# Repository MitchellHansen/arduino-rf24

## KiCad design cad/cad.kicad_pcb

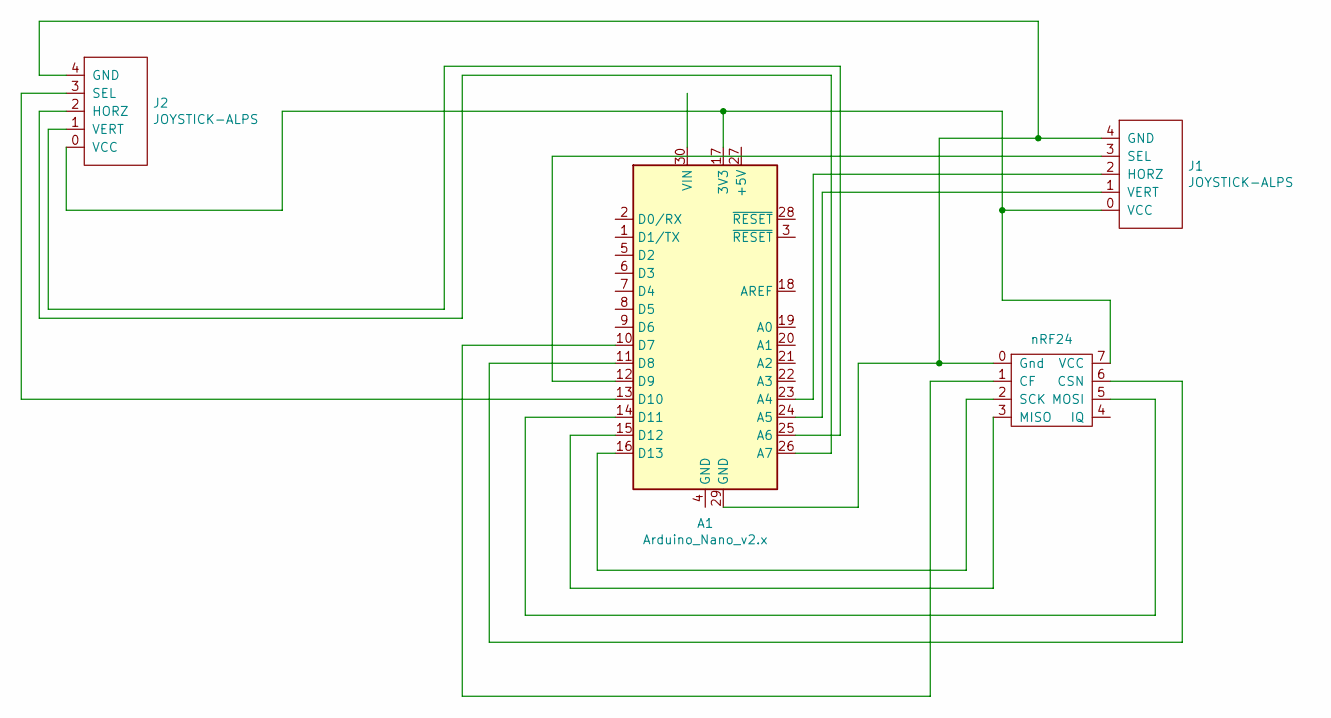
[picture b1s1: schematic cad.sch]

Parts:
A1: Arduino_Nano_v2.x; Arduino_Nano
J1, J2: JOYSTICK-ALPS
U1: nRF24

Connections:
unnamed: A1.10 (D7), U1.1 (CF)
unnamed: A1.11 (D8), U1.6 (CSN)
unnamed: A1.12 (D9), J1.3 (SEL)
unnamed: A1.13 (D10), J2.3 (SEL)
unnamed: A1.14 (D11), U1.5 (MOSI)
unnamed: A1.15 (D12), U1.3 (MISO)
unnamed: A1.16 (D13), U1.2 (SCK)
unnamed: A1.17 (3V3), J1.0 (VCC), J2.0 (VCC), U1.7 (VCC)
unnamed: A1.23 (A4), J1.2 (HORZ)
unnamed: A1.24 (A5), J1.1 (VERT)
unnamed: A1.25 (A6), J2.1 (VERT)
unnamed: A1.26 (A7), J2.2 (HORZ)
unnamed: A1.29 (GND), J1.4 (GND), J2.4 (GND), U1.0 (Gnd)

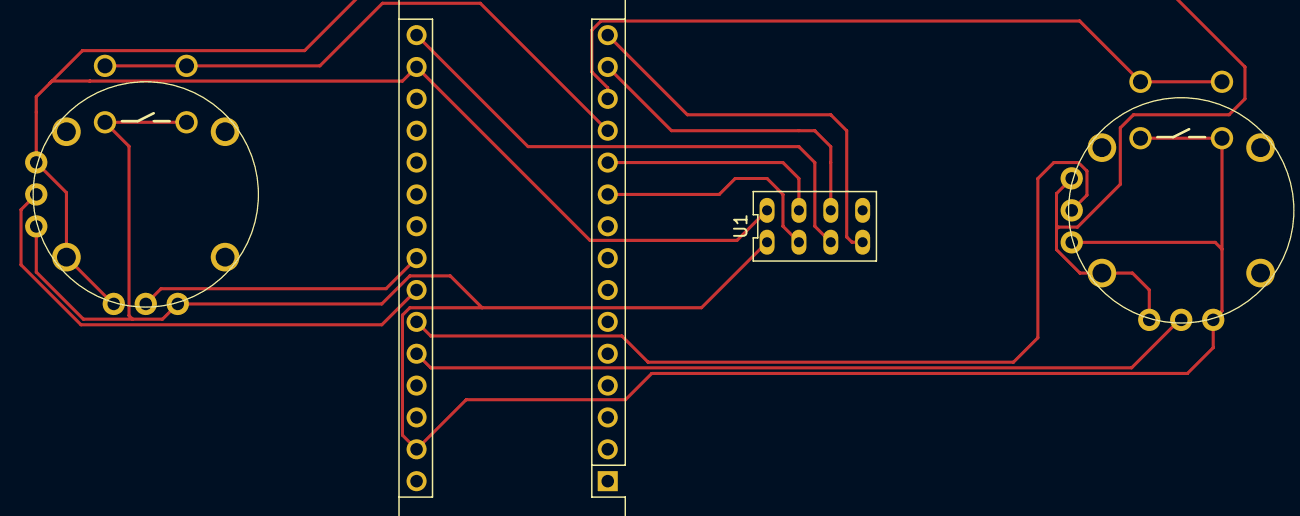
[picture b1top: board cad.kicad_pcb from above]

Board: 2 copper layers, 4 parts (0 on the bottom side), 13 nets.

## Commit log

2019-03-28 init
2019-04-14 Added IR distance code
2020-01-27 have arduino imported, and RF24 compiling
2020-02-02 added arduino, modified build
2020-02-03 removed intermediate files
2020-02-03 cmake instead of make
2020-02-03 remove wonky submodule
2020-02-03 remove old build system
2020-02-03 name the hex main
2020-02-03 removing some arduino libraries
2020-02-03 don't need that either
2020-09-16 cad files
